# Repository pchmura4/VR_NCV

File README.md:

# VR_NCV
Speeduino compatible Variable Reluctance adapter based on cheap NCV1124 integrated circuit.  
The low-pass filter on the input needs to be tuned to for the actual sensor (R1-C1 and R2-C2 for respective channels).  
See [datasheet](https://www.onsemi.com/pub/Collateral/NCV1124%20DATA%20SHEET.PDF)

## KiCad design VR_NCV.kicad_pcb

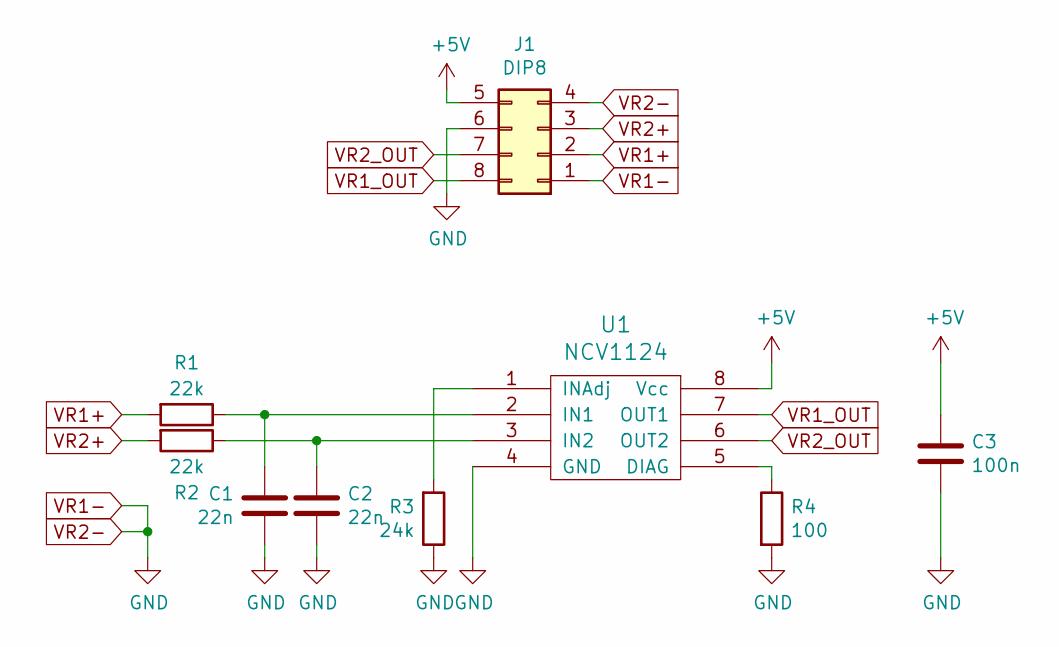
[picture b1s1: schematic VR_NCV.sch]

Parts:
C1, C2: 22n; C_0805_2012Metric_Pad1.15x1.40mm_HandSolder
C3: 100n; C_0805_2012Metric_Pad1.15x1.40mm_HandSolder
J1: DIP8; DIP-8_W7.62mm_Socket_LongPads
R1, R2: 22k; R_2512_6332Metric_Pad1.52x3.35mm_HandSolder
R3: 24k; R_1206_3216Metric_Pad1.42x1.75mm_HandSolder
R4: 100; R_1206_3216Metric_Pad1.42x1.75mm_HandSolder
U1: NCV1124

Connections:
+5V: C3.1, J1.5, U1.8 (Vcc)
unnamed: C1.2, R1.1, U1.2 (IN1)
unnamed: C2.1, R2.1, U1.3 (IN2)
unnamed: R3.2, U1.1 (INAdj)
unnamed: R4.1, U1.5 (DIAG)
VR1+: J1.2, R1.2
VR1-: C1.1, C2.2, C3.2, J1.1, J1.4, J1.6, R3.1, R4.2, U1.4 (GND)
VR1_OUT: J1.8, U1.7 (OUT1)
VR2+: J1.3, R2.2
VR2_OUT: J1.7, U1.6 (OUT2)

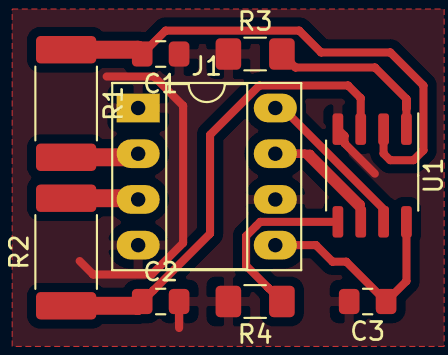
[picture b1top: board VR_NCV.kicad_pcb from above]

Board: 2 copper layers, 9 parts (0 on the bottom side), 10 nets.

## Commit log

2021-02-14 Add board render
